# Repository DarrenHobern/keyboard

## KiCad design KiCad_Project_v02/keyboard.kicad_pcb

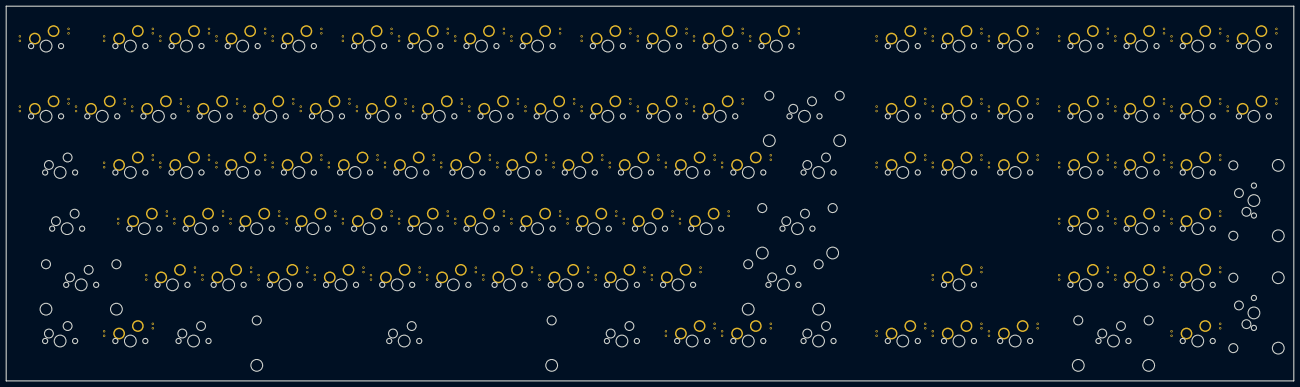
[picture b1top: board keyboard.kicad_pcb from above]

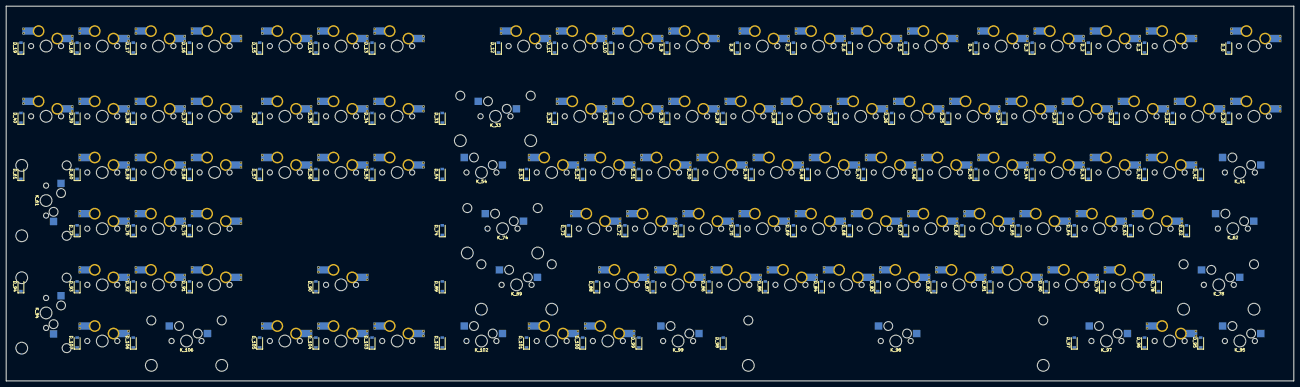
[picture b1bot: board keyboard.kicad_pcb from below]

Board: 2 copper layers, 436.6 x 127.1 mm, 216 parts (108 on the bottom side), 136 nets, no tracks yet.

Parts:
D_0, D_1, D_2, D_3, D_4, D_5, D_6, D_7, D_8, D_9, D_10, D_11, D_12, D_13, D_14, D_15, D_16, D_17, D_18, D_19, D_20, D_21, D_22, D_23, D_24, D_25, D_26, D_27, D_28, D_29, D_30, D_31, D_32, D_33, D_34, D_35, D_36, D_37, D_38, D_39, D_40, D_41, D_42, D_43, D_44, D_45, D_46, D_47, D_48, D_49, D_50, D_51, D_52, D_53, D_54, D_55, D_56, D_57, D_58, D_59, D_60, D_61, D_62, D_63, D_64, D_65, D_66, D_67, D_68, D_69, D_70, D_71, D_72, D_73, D_74, D_75, D_76, D_77, D_78, D_79, D_80, D_81, D_82, D_83, D_84, D_85, D_86, D_87, D_88, D_89, D_90, D_91, D_92, D_93, D_94, D_95, D_96, D_97, D_98, D_99, D_100, D_101, D_102, D_103, D_104, D_105, D_106, D_107: D; D_SOD-123
K_0, K_1, K_2, K_3, K_4, K_5, K_6, K_7, K_8, K_9, K_10, K_11, K_12, K_13, K_14, K_15, K_16, K_17, K_18, K_19, K_20, K_21, K_22, K_23, K_24, K_25, K_26, K_27, K_28, K_29, K_30, K_31, K_32, K_34, K_35, K_36, K_37, K_38, K_39, K_40, K_42, K_43, K_44, K_45, K_46, K_47, K_48, K_49, K_50, K_51, K_52, K_53, K_55, K_56, K_57, K_58, K_59, K_60, K_63, K_64, K_65, K_66, K_67, K_68, K_69, K_70, K_71, K_72, K_73, K_75, K_76, K_77, K_79, K_80, K_81, K_82, K_83, K_84, K_85, K_86, K_87, K_88, K_90, K_91, K_92, K_93, K_96, K_100, K_101, K_103, K_104, K_105, K_107: KEYSW; MXOnly-1U-Hotswap-Antishear
K_33, K_61, K_94, K_106: KEYSW; MXOnly-2U-Hotswap
K_41, K_54, K_95, K_99, K_102: KEYSW; MXOnly-1.5U-Hotswap
K_62: KEYSW; MXOnly-1.75U-Hotswap
K_74, K_78: KEYSW; MXOnly-2.25U-Hotswap
K_89: KEYSW; MXOnly-2.75U-Hotswap
K_97: KEYSW; MXOnly-1.25U-Hotswap
K_98: KEYSW; MXOnly-6.25U-Hotswap

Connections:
unnamed: D_0.2, K_0.2
unnamed: D_1.2, K_1.2
unnamed: D_2.2, K_2.2
unnamed: D_3.2, K_3.2
unnamed: D_4.2, K_4.2
unnamed: D_5.2, K_5.2
unnamed: D_6.2, K_6.2
unnamed: D_7.2, K_7.2
unnamed: D_8.2, K_8.2
unnamed: D_9.2, K_9.2
unnamed: D_10.2, K_10.2
unnamed: D_11.2, K_11.2
unnamed: D_12.2, K_12.2
unnamed: D_13.2, K_13.2
unnamed: D_14.2, K_14.2
unnamed: D_15.2, K_15.2
unnamed: D_16.2, K_16.2
unnamed: D_17.2, K_17.2
unnamed: D_18.2, K_18.2
unnamed: D_19.2, K_19.2
unnamed: D_20.2, K_20.2
unnamed: D_21.2, K_21.2
unnamed: D_22.2, K_22.2
unnamed: D_23.2, K_23.2
unnamed: D_24.2, K_24.2
unnamed: D_25.2, K_25.2
unnamed: D_26.2, K_26.2
unnamed: D_27.2, K_27.2
unnamed: D_28.2, K_28.2
unnamed: D_29.2, K_29.2
unnamed: D_30.2, K_30.2
unnamed: D_31.2, K_31.2
unnamed: D_32.2, K_32.2
unnamed: D_33.2, K_33.2
unnamed: D_34.2, K_34.2
unnamed: D_35.2, K_35.2
unnamed: D_36.2, K_36.2
unnamed: D_37.2, K_37.2
unnamed: D_38.2, K_38.2
unnamed: D_39.2, K_39.2
unnamed: D_40.2, K_40.2
unnamed: D_41.2, K_41.2
unnamed: D_42.2, K_42.2
unnamed: D_43.2, K_43.2
unnamed: D_44.2, K_44.2
unnamed: D_45.2, K_45.2
unnamed: D_46.2, K_46.2
unnamed: D_47.2, K_47.2
unnamed: D_48.2, K_48.2
unnamed: D_49.2, K_49.2
unnamed: D_50.2, K_50.2
unnamed: D_51.2, K_51.2
unnamed: D_52.2, K_52.2
unnamed: D_53.2, K_53.2
unnamed: D_54.2, K_54.2
unnamed: D_55.2, K_55.2
unnamed: D_56.2, K_56.2
unnamed: D_57.2, K_57.2
unnamed: D_58.2, K_58.2
unnamed: D_59.2, K_59.2
unnamed: D_60.2, K_60.2
unnamed: D_61.2, K_61.2
unnamed: D_62.2, K_62.2
unnamed: D_63.2, K_63.2
unnamed: D_64.2, K_64.2
unnamed: D_65.2, K_65.2
unnamed: D_66.2, K_66.2
unnamed: D_67.2, K_67.2
unnamed: D_68.2, K_68.2
unnamed: D_69.2, K_69.2
unnamed: D_70.2, K_70.2
unnamed: D_71.2, K_71.2
unnamed: D_72.2, K_72.2
unnamed: D_73.2, K_73.2
unnamed: D_74.2, K_74.2
unnamed: D_75.2, K_75.2
unnamed: D_76.2, K_76.2
unnamed: D_77.2, K_77.2
unnamed: D_78.2, K_78.2
unnamed: D_79.2, K_79.2
unnamed: D_80.2, K_80.2
unnamed: D_81.2, K_81.2
unnamed: D_82.2, K_82.2
unnamed: D_83.2, K_83.2
unnamed: D_84.2, K_84.2
unnamed: D_85.2, K_85.2
unnamed: D_86.2, K_86.2
unnamed: D_87.2, K_87.2
unnamed: D_88.2, K_88.2
unnamed: D_89.2, K_89.2
unnamed: D_90.2, K_90.2
unnamed: D_91.2, K_91.2
unnamed: D_92.2, K_92.2
unnamed: D_93.2, K_93.2
unnamed: D_94.2, K_94.2
unnamed: D_95.2, K_95.2
unnamed: D_96.2, K_96.2
unnamed: D_97.2, K_97.2
unnamed: D_98.2, K_98.2
unnamed: D_99.2, K_99.2
unnamed: D_100.2, K_100.2
unnamed: D_101.2, K_101.2
unnamed: D_102.2, K_102.2
unnamed: D_103.2, K_103.2
unnamed: D_104.2, K_104.2
unnamed: D_105.2, K_105.2
unnamed: D_106.2, K_106.2
unnamed: D_107.2, K_107.2
col0: K_0.1, K_20.1, K_41.1, K_62.1, K_95.1
col1: K_21.1, K_78.1
col2: K_1.1, K_22.1, K_42.1, K_63.1, K_79.1, K_96.1
col3: K_2.1, K_23.1, K_43.1, K_64.1, K_80.1, K_97.1
col4: K_3.1, K_24.1, K_44.1, K_65.1, K_81.1
col5: K_4.1, K_25.1, K_45.1, K_66.1, K_82.1
col6: K_5.1, K_26.1, K_46.1, K_67.1, K_83.1, K_98.1
col7: K_6.1, K_27.1, K_47.1, K_68.1, K_84.1
col8: K_7.1, K_28.1, K_48.1, K_69.1, K_85.1
col9: K_8.1, K_29.1, K_49.1, K_70.1, K_86.1
col10: K_9.1, K_30.1, K_50.1, K_71.1, K_87.1, K_99.1
col11: K_10.1, K_31.1, K_51.1, K_72.1, K_88.1
col12: K_11.1, K_32.1, K_52.1, K_73.1, K_100.1
col13: K_12.1, K_53.1, K_74.1, K_89.1, K_101.1
col14: K_33.1, K_54.1, K_102.1
col15: K_13.1, K_34.1, K_55.1, K_103.1
col16: K_14.1, K_35.1, K_56.1, K_90.1, K_104.1
col17: K_15.1, K_36.1, K_57.1, K_105.1
col18: K_16.1, K_37.1, K_58.1, K_75.1, K_91.1, K_106.1
col19: K_17.1, K_38.1, K_59.1, K_76.1, K_92.1
col20: K_18.1, K_39.1, K_60.1, K_77.1, K_93.1, K_107.1
col21: K_19.1, K_40.1, K_61.1, K_94.1
row0: D_0.1, D_1.1, D_2.1, D_3.1, D_4.1, D_5.1, D_6.1, D_7.1, D_8.1, D_9.1, D_10.1, D_11.1, D_12.1, D_13.1, D_14.1, D_15.1, D_16.1, D_17.1, D_18.1, D_19.1
row1: D_20.1, D_21.1, D_22.1, D_23.1, D_24.1, D_25.1, D_26.1, D_27.1, D_28.1, D_29.1, D_30.1, D_31.1, D_32.1, D_33.1, D_34.1, D_35.1, D_36.1, D_37.1, D_38.1, D_39.1, D_40.1
row2: D_41.1, D_42.1, D_43.1, D_44.1, D_45.1, D_46.1, D_47.1, D_48.1, D_49.1, D_50.1, D_51.1, D_52.1, D_53.1, D_54.1, D_55.1, D_56.1, D_57.1, D_58.1, D_59.1, D_60.1
row3: D_61.1, D_62.1, D_63.1, D_64.1, D_65.1, D_66.1, D_67.1, D_68.1, D_69.1, D_70.1, D_71.1, D_72.1, D_73.1, D_74.1, D_75.1, D_76.1, D_77.1
row4: D_78.1, D_79.1, D_80.1, D_81.1, D_82.1, D_83.1, D_84.1, D_85.1, D_86.1, D_87.1, D_88.1, D_89.1, D_90.1, D_91.1, D_92.1, D_93.1
row5: D_94.1, D_95.1, D_96.1, D_97.1, D_98.1, D_99.1, D_100.1, D_101.1, D_102.1, D_103.1, D_104.1, D_105.1, D_106.1, D_107.1

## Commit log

2020-12-19 init commit
